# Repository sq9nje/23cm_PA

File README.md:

# Power Amplifier for the 23cm Band
This is a simple power amplifier for the 23cm HAM band. It uses the 18W RA18H1213G module from Mitsubishi as the active device.

## Interactive BOM
Interactive BOM is available [here](https://htmlpreview.github.io/?https://github.com/sq9nje/23cm_PA/blob/master/bom/ibom.html)

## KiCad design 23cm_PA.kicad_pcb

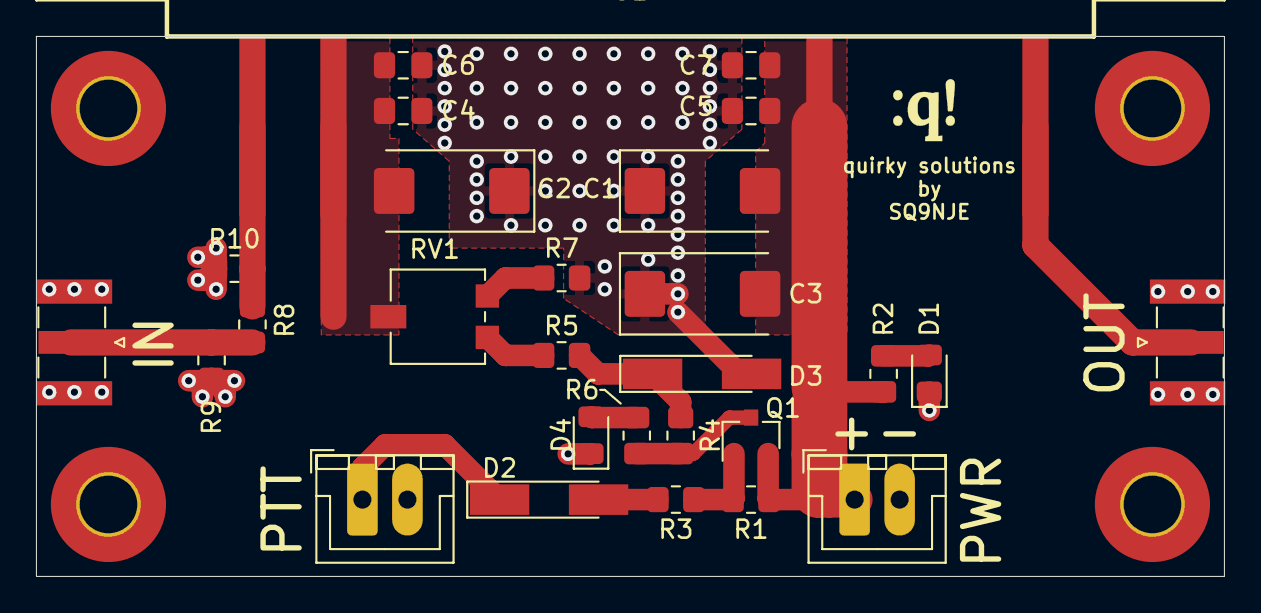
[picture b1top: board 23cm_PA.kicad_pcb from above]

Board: 2 copper layers, 66.0 x 30.0 mm, 33 parts (0 on the bottom side), 15 nets.

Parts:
C1, C2, C3: 22u; CP_EIA-7343-31_Kemet-D_Pad2.25x2.55mm_HandSolder
C4, C5: 100n; C_0805_2012Metric_Pad1.18x1.45mm_HandSolder
C6, C7: 1n; C_0805_2012Metric_Pad1.18x1.45mm_HandSolder
D1, D4: LED_Small; LED_0805_2012Metric_Pad1.15x1.40mm_HandSolder
D2: 1N4148; D_MiniMELF_Handsoldering
D3: 6.2V; D_MiniMELF_Handsoldering
H1, H2, H3, H4: MountingHole_Pad; MountingHole_3.2mm_M3_Pad_TopBottom
J1, J2: Conn_01x02; JST_XH_B2B-XH-A_1x02_P2.50mm_Vertical
J3, J4: Conn_Coaxial; SMA_Samtec_SMA-J-P-X-ST-EM1_EdgeMount
Q1: BC807; SOT-23
R1: 510; R_0805_2012Metric_Pad1.20x1.40mm_HandSolder
R2, R3, R6: 5.1k; R_0805_2012Metric_Pad1.20x1.40mm_HandSolder
R4: 330; R_0805_2012Metric_Pad1.20x1.40mm_HandSolder
R5, R7: 220; R_0805_2012Metric_Pad1.20x1.40mm_HandSolder
R8: 18; R_0805_2012Metric_Pad1.20x1.40mm_HandSolder
R9, R10: 300; R_0805_2012Metric_Pad1.20x1.40mm_HandSolder
RV1: 10k; Potentiometer_Vishay_TS53YL_Vertical
Ref**: Val**; qs_logo
U1: RA18H1213G

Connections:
+12V: C1.2, C3.2, C5.2, C7.2, J2.1, Q1.2, R1.1, R2.1, U1.3
GND: C1.1, C2.1, C3.1, C4.2, C5.1, C6.2, C7.1, D1.1, D3.2, D4.1, H1.1, H2.1, H3.1, H4.1, J1.2, J2.2, J3.2, J4.2, R7.2, R9.2, R10.2
unnamed: C2.2, C4.1, C6.1, RV1.2, U1.2
unnamed: D1.2, R2.2
unnamed: D2.1, J1.1
unnamed: D2.2, R3.2
unnamed: D3.1, R4.1, R5.1
unnamed: D4.2, R6.1
unnamed: J3.1, U1.4
unnamed: J4.1, R8.2, R9.1
unnamed: Q1.1, R1.2, R3.1
unnamed: Q1.3, R4.2, R6.2
unnamed: R5.2, RV1.3
unnamed: R7.1, RV1.1
unnamed: R8.1, R10.1, U1.1

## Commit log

2021-09-19 initial design
